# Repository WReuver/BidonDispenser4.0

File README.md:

# Bidon Dispenser 4.0
_Smart Solutions Semester - Join the Pipe - Year 17/18 - Semester 02_

### Authors
All the software is written by Robin C. Pel with student number 421 431. 
All the hardware is designed by Glen te Hofsté with student number 419 720. 

### Note to self
Use "git merge --allow-unrelated-histories [ORPHAN-BRANCH]" to merge orphan branches.

### While Loops
All the while loops in the Microcontroller's program:
- "./Communication/OneWire.cpp" line 13: Wait for a pin to be high
- "./Communication/USART.cpp" line 34: Wait for new data on the serial port
- "./Communication/USART.cpp" line 42: Wait for new data on the serial port for 2 seconds
- "./Hardware/SystemClock.cpp" line 13: Wait for the clock source to be ready
- "./Master/RaspberryPi.cpp" line 36: Wait until the pre-amble is found
- "./Sensors/DistanceSensor.cpp" line 93: Wait for a pin to be high
- "./Sensors/DistanceSensor.cpp" line 93: Wait for a pin to be low
- "./Sensors/TemperatureSensor.cpp" line 33: Wait for a pin to be high
- "./main.cpp" line 197, 280, 323, 362 and 384: Infinite loops

### Important
Not all code on the "microcontroller/software/develop" branch works with all the microcontroller hardware:  
	- All the commits **BEFORE** the tag "MCU_Festival" only work on the controller PCB v1.1  
	- All the commits **AFTER** the tag "MCU_Festival" only work on the controller PCB v2.0  
  
Another thing that's definitely worth mentioning is that on the microcontroller PCB v1.1 the ADC was used to read a 1 or 0.
This was done because for some weird reason it was not possible to read one of the digital pins, 
the microcontroller probably was broken or something but the decision was made to work around it for the time being.  
  
After the Smart Solutions Festival one of the distance sensors broke, this sensor was distance sensor number five.  
Distance Sensor Layout Layout (Top view, from the front):  
_Dist Sensor: [08] [01] [10] [03] [12] [05] [14] [07]_  
_Dist Sensor: [00] [09] [02] [11] [04] [13] [06] [15]_  

### Disclaimer
This was my first experience with C# and the Visual Studio IDE, there are probably a lot of things which could be optimized. 
This git repo was also misused a little bit, apologies. 
There is _no_ easter egg. 

### Regarding the UI Assets
All UI Assets were made using Paint dot net, you can get it here https://www.dotpdn.com/downloads/pdn.html

### The Team 💪

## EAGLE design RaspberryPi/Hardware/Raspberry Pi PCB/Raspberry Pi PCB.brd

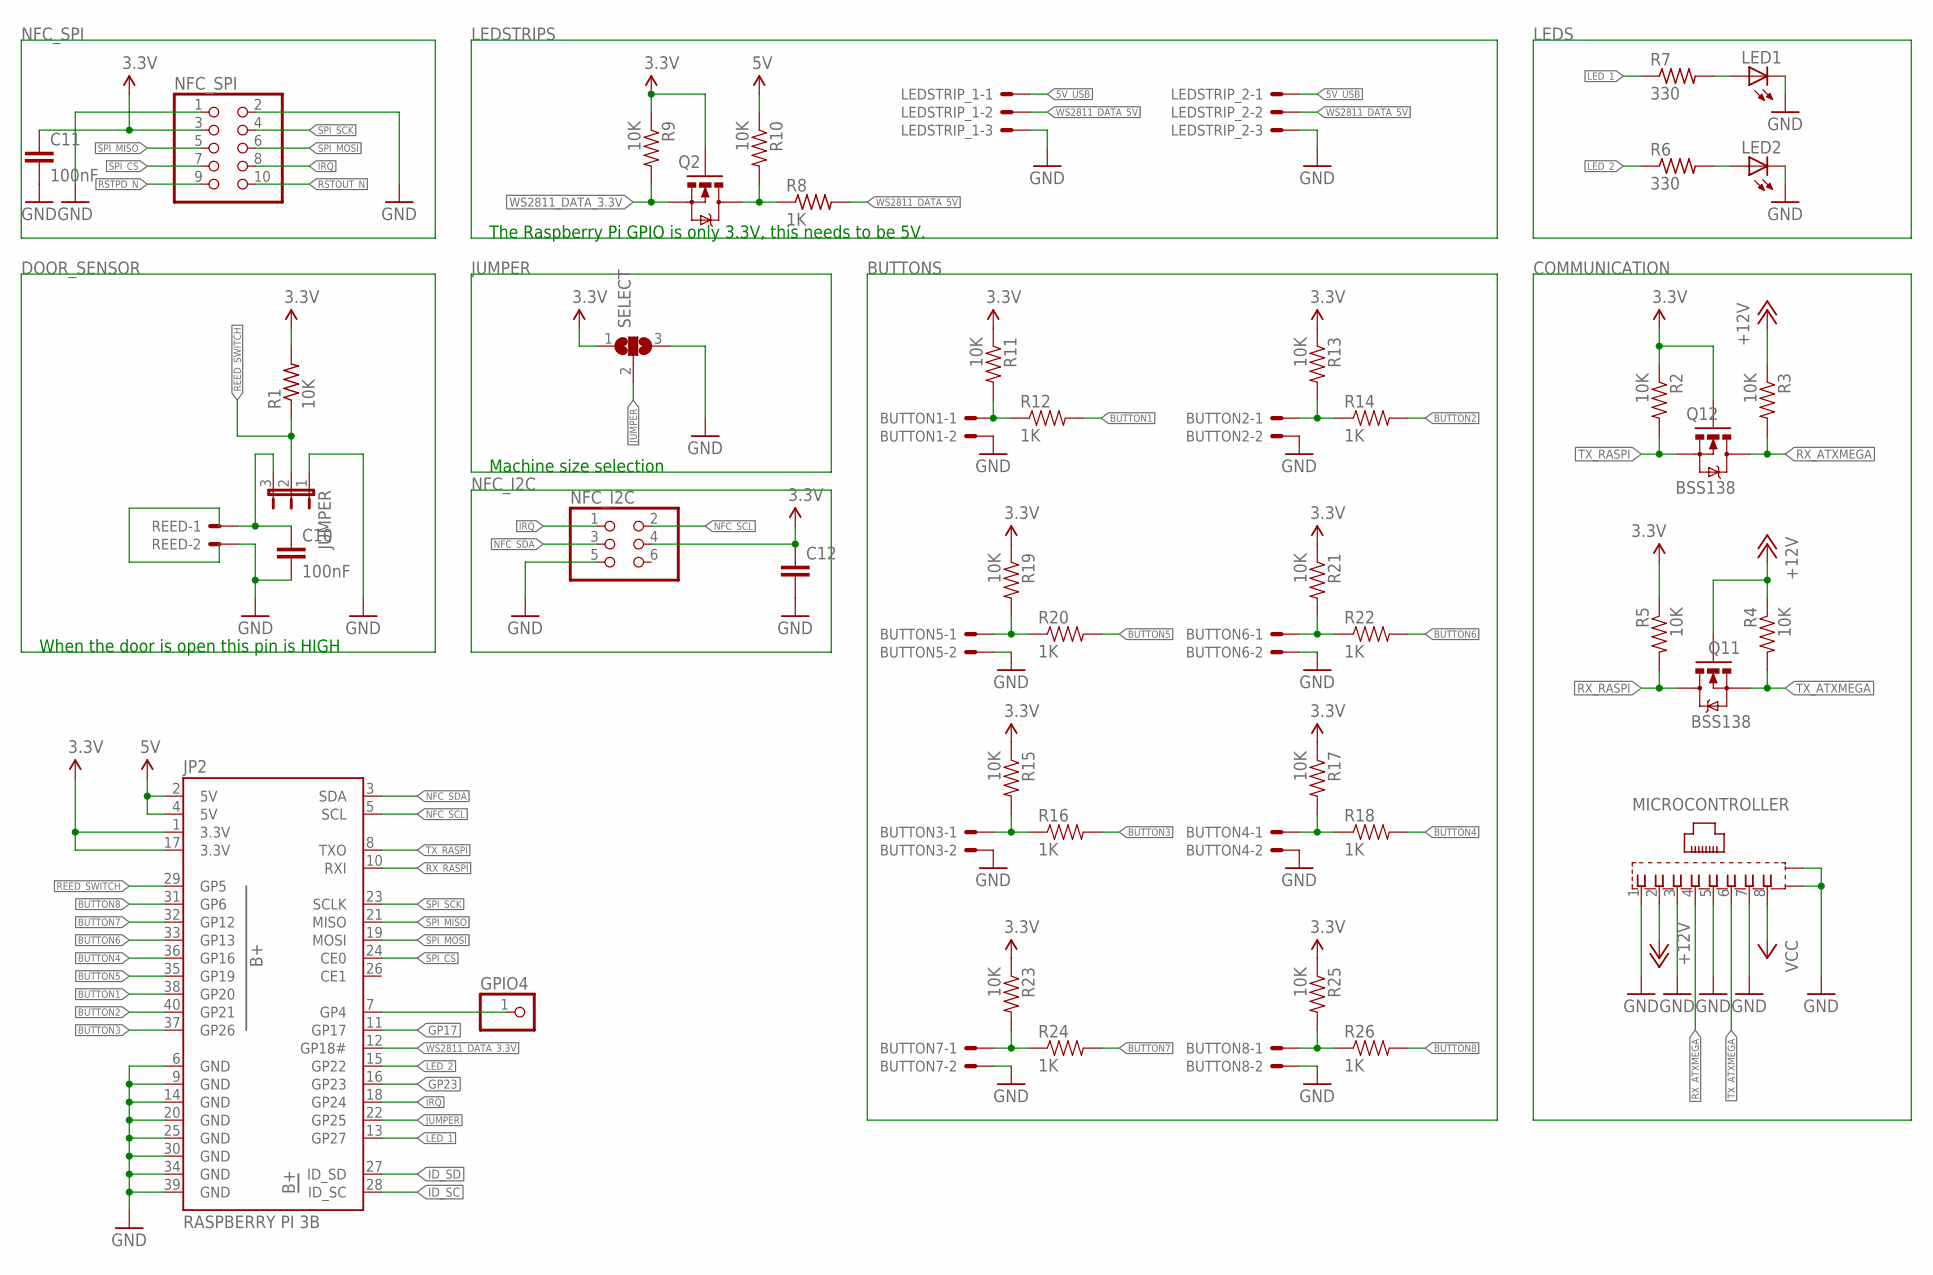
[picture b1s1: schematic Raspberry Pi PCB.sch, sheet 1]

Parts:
BUTTON1, BUTTON2, BUTTON3, BUTTON4, BUTTON5, BUTTON6, BUTTON7, BUTTON8: 22-05-7028-02; 7395-02
C10, C11, C12: 100nF; 0805
GPIO4: PINHD-1X1; 1X01
JP2: RASPBERRY PI 3B; 2X20-SHROUDED
JUMPER: JP2E; JP2
LED1, LED2: LEDCHIPLED_0805; CHIPLED_0805
LEDSTRIP_1, LEDSTRIP_2: 22-05-7038-03; 7395-03
MICROCONTROLLER: 0446200002
NFC_I2C: PINHD-2X3; 2X03
NFC_SPI: PINHD-2X5; 2X05
Q2, Q11, Q12: BSS138; SOT23-3
R1: 10K; R0805
R2, R3, R4, R5, R9, R10, R11, R13, R15, R17, R19, R21, R23, R25: 10K; 0603-RES
R6, R7: 330; R0805
R8: 1K; R0805
R12, R14, R16, R18, R20, R22, R24, R26: 1K; 0603-RES
REED: 22-05-7028-02; 7395-02
SELECT: SJ2W; SJ_2

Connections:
3.3V: C11.1, C12.1, JP2.1 (3.3V), JP2.17 (3.3V), NFC_I2C.4, NFC_SPI.3, Q2.1 (G), Q12.1 (G), R1.2, R2.1, R5.1, R9.1, R11.1, R13.1, R15.1, R17.1, R19.1, R21.1, R23.1, R25.1, SELECT.1
5V: JP2.2 (5V), JP2.4 (5V), R10.1; also elsewhere on the board
5V_USB: LEDSTRIP_1.1, LEDSTRIP_2.1; also elsewhere on the board
+12V: MICROCONTROLLER.2, Q11.1 (G), R3.1, R4.1
BUTTON1: JP2.38 (GP20), R12.2
BUTTON2: JP2.40 (GP21), R14.2
BUTTON3: JP2.37 (GP26), R16.2
BUTTON4: JP2.36 (GP16), R18.2
BUTTON5: JP2.35 (GP19), R20.2
BUTTON6: JP2.33 (GP13), R22.2
BUTTON7: JP2.32 (GP12), R24.2
BUTTON8: JP2.31 (GP6), R26.2
GND: BUTTON1.2, BUTTON2.2, BUTTON3.2, BUTTON4.2, BUTTON5.2, BUTTON6.2, BUTTON7.2, BUTTON8.2, C10.2, C11.2, C12.2, JP2.6 (GND), JP2.9 (GND), JP2.14 (GND), JP2.20 (GND), JP2.25 (GND), JP2.30 (GND), JP2.34 (GND), JP2.39 (GND), JUMPER.1, LED1.C, LED2.C, LEDSTRIP_1.3, LEDSTRIP_2.3, MICROCONTROLLER.1, MICROCONTROLLER.3, MICROCONTROLLER.5, MICROCONTROLLER.7, MICROCONTROLLER.S@1 (S1), MICROCONTROLLER.S@2 (S2), NFC_I2C.5, NFC_SPI.1, NFC_SPI.2, REED.2, SELECT.3; also elsewhere on the board
GP4: GPIO4.1, JP2.7 (GP4)
GP17: JP2.11 (GP17)
GP23: JP2.16 (GP23)
ID_SC: JP2.28 (ID_SC)
ID_SD: JP2.27 (ID_SD)
IRQ: JP2.18 (GP24), NFC_I2C.1, NFC_SPI.8
JUMPER: JP2.22 (GP25), SELECT.2
LED_1: JP2.13 (GP27), R7.1
LED_2: JP2.15 (GP22), R6.1
unnamed: C10.1, JUMPER.3, REED.1
unnamed: BUTTON2.1, R13.2, R14.1
unnamed: Q2.3 (D), R8.1, R10.2
unnamed: LED2.A, R6.2
unnamed: LED1.A, R7.2
unnamed: BUTTON1.1, R11.2, R12.1
unnamed: BUTTON3.1, R15.2, R16.1
unnamed: BUTTON4.1, R17.2, R18.1
unnamed: BUTTON5.1, R19.2, R20.1
unnamed: BUTTON6.1, R21.2, R22.1
unnamed: BUTTON7.1, R23.2, R24.1
unnamed: BUTTON8.1, R25.2, R26.1
NFC_SCL: JP2.5 (SCL), NFC_I2C.2
NFC_SDA: JP2.3 (SDA), NFC_I2C.3
REED_SWITCH: JP2.29 (GP5), JUMPER.2, R1.1
RSTOUT_N: NFC_SPI.10
RSTPD_N: NFC_SPI.9
RX_ATXMEGA: MICROCONTROLLER.4, Q12.3 (D), R3.2
RX_RASPI: JP2.10 (RXI), Q11.3 (D), R5.2
SPI_CS: JP2.24 (CE0), NFC_SPI.7
SPI_MISO: JP2.21 (MISO), NFC_SPI.5
SPI_MOSI: JP2.19 (MOSI), NFC_SPI.6
SPI_SCK: JP2.23 (SCLK), NFC_SPI.4
TX_ATXMEGA: MICROCONTROLLER.6, Q11.2 (S), R4.2
TX_RASPI: JP2.8 (TXO), Q12.2 (S), R2.2
VCC: MICROCONTROLLER.8
WS2811_DATA_3.3V: JP2.12 (GP18#), Q2.2 (S), R9.2
WS2811_DATA_5V: LEDSTRIP_1.2, LEDSTRIP_2.2, R8.2

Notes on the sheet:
Machine size selection
When the door is open this pin is HIGH
The Raspberry Pi GPIO is only 3.3V, this needs to be 5V.

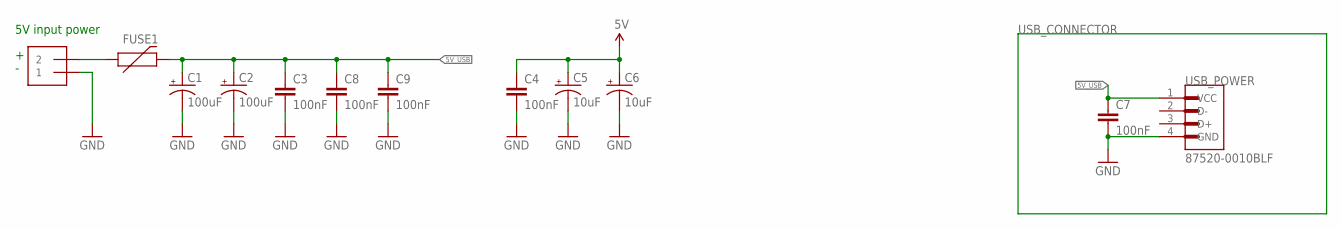
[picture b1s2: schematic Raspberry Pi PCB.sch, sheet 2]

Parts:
C1, C2: 100uF; 175TMP-0810
C3, C4, C7, C8, C9: 100nF; 0805
C5, C6: 10uF; 153CLV-0505
FUSE1: 6V/0.5A; 1206
INPUT: 1X2-3.5MM
USB_POWER: 87520-0010BLF; FCI_87520-0010BLF

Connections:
5V: C4.1, C5.+, C6.+; also elsewhere on the board
5V_USB: C1.+, C2.+, C3.1, C7.1, C8.1, C9.1, FUSE1.2, USB_POWER.1 (VCC); also elsewhere on the board
GND: C1.-, C2.-, C3.2, C4.2, C5.-, C6.-, C7.2, C8.2, C9.2, INPUT.1, USB_POWER.4 (GND); also elsewhere on the board
VIN1: FUSE1.1, INPUT.2

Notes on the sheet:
5V input power

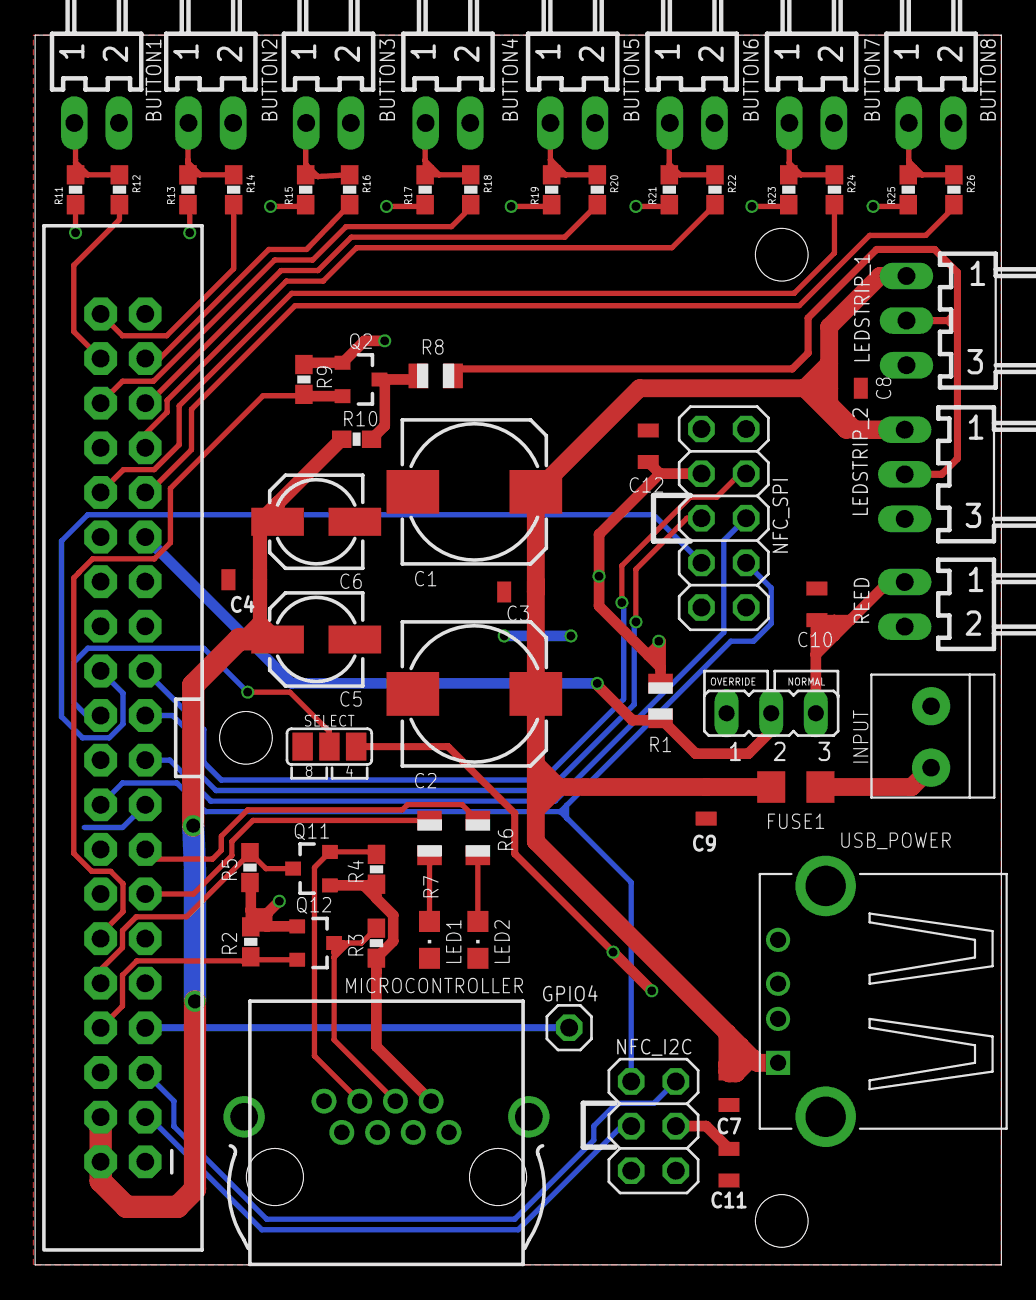
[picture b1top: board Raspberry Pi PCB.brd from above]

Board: 2 copper layers, 55.0 x 70.0 mm, 64 parts (0 on the bottom side), 44 nets.

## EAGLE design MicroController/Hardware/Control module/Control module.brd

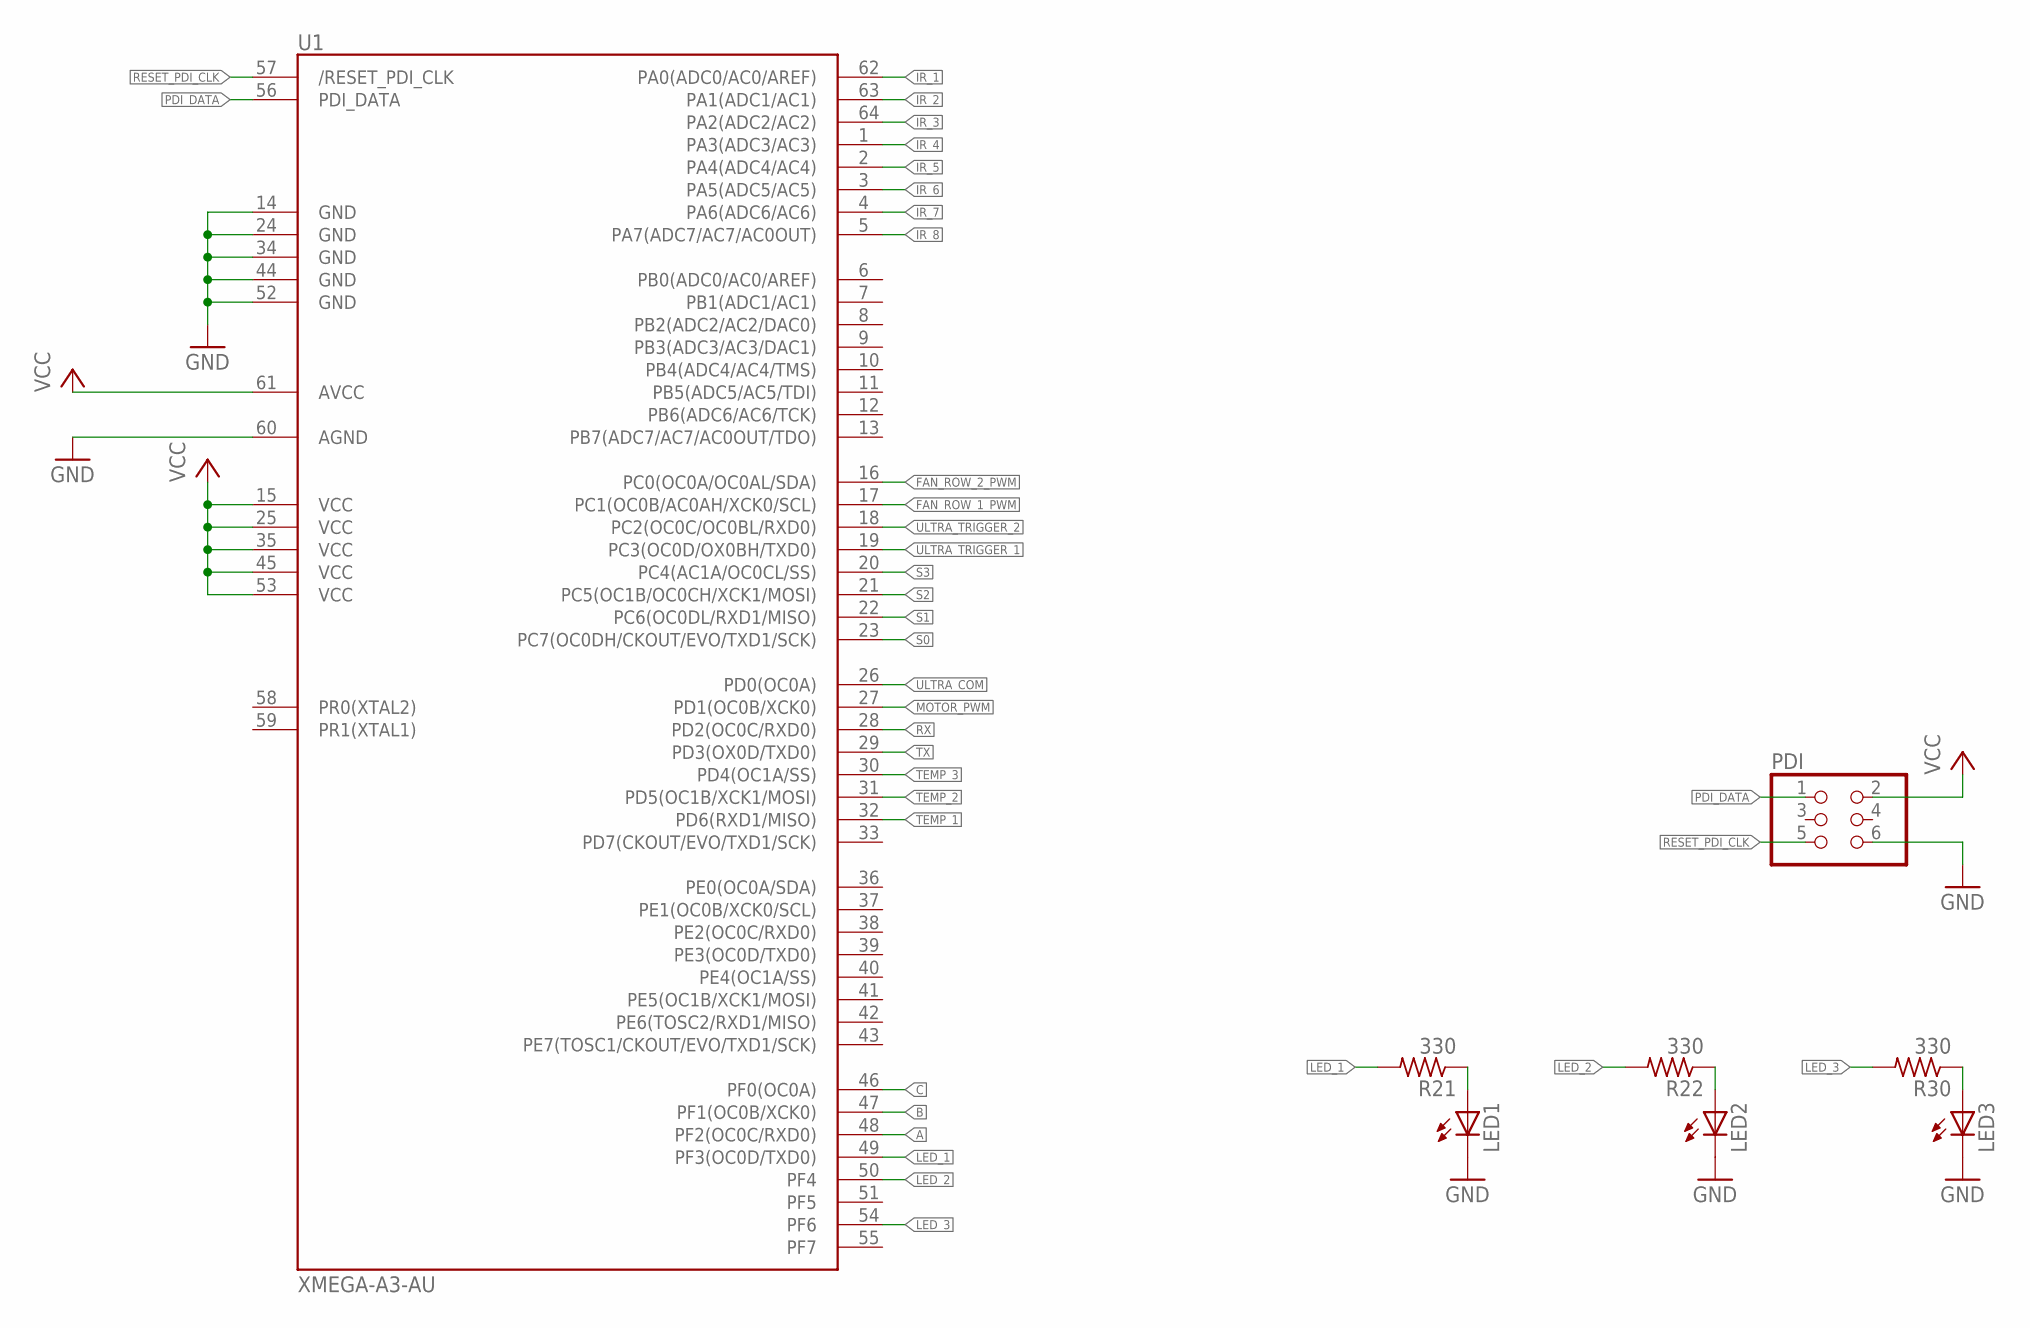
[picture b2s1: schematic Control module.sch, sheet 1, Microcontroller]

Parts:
LED1, LED2, LED3: LEDCHIPLED_0805; CHIPLED_0805
PDI: PINHD-2X3; 2X03
R21, R22, R30: 330; R0805
U1: XMEGA-A3-AU; TQFP64_14X14MM_MCU

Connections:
A: U1.48 (PF2(OC0C/RXD0)); also elsewhere on the board
B: U1.47 (PF1(OC0B/XCK0)); also elsewhere on the board
C: U1.46 (PF0(OC0A)); also elsewhere on the board
FAN_ROW_1_PWM: U1.17 (PC1(OC0B/AC0AH/XCK0/SCL)); also elsewhere on the board
FAN_ROW_2_PWM: U1.16 (PC0(OC0A/OC0AL/SDA)); also elsewhere on the board
GND: LED1.C, LED2.C, LED3.C, PDI.6, U1.14 (GND1), U1.24 (GND2), U1.34 (GND3), U1.44 (GND4), U1.52 (GND5), U1.60 (AGND); also elsewhere on the board
IR_1: U1.62 (PA0(ADC0/AC0/AREF)); also elsewhere on the board
IR_2: U1.63 (PA1(ADC1/AC1)); also elsewhere on the board
IR_3: U1.64 (PA2(ADC2/AC2)); also elsewhere on the board
IR_4: U1.1 (PA3(ADC3/AC3)); also elsewhere on the board
IR_5: U1.2 (PA4(ADC4/AC4)); also elsewhere on the board
IR_6: U1.3 (PA5(ADC5/AC5)); also elsewhere on the board
IR_7: U1.4 (PA6(ADC6/AC6)); also elsewhere on the board
IR_8: U1.5 (PA7(ADC7/AC7/AC0OUT)); also elsewhere on the board
LED_1: R21.2, U1.49 (PF3(OC0D/TXD0))
LED_2: R22.2, U1.50 (PF4)
LED_3: R30.2, U1.54 (PF6)
MOTOR_PWM: U1.27 (PD1(OC0B/XCK0)); also elsewhere on the board
unnamed: LED2.A, R22.1
unnamed: LED1.A, R21.1
unnamed: LED3.A, R30.1
PDI_DATA: PDI.1, U1.56 (PDI_DATA)
RESET_PDI_CLK: PDI.5, U1.57 (/RESET_PDI_CLK)
RX: U1.28 (PD2(OC0C/RXD0)); also elsewhere on the board
S0: U1.23 (PC7(OC0DH/CKOUT/EVO/TXD1/SCK)); also elsewhere on the board
S1: U1.22 (PC6(OC0DL/RXD1/MISO)); also elsewhere on the board
S2: U1.21 (PC5(OC1B/OC0CH/XCK1/MOSI)); also elsewhere on the board
S3: U1.20 (PC4(AC1A/OC0CL/SS)); also elsewhere on the board
TEMP_1: U1.32 (PD6(RXD1/MISO)); also elsewhere on the board
TEMP_2: U1.31 (PD5(OC1B/XCK1/MOSI)); also elsewhere on the board
TEMP_3: U1.30 (PD4(OC1A/SS)); also elsewhere on the board
TX: U1.29 (PD3(OX0D/TXD0)); also elsewhere on the board
ULTRA_COM: U1.26 (PD0(OC0A)); also elsewhere on the board
ULTRA_TRIGGER_1: U1.19 (PC3(OC0D/OX0BH/TXD0)); also elsewhere on the board
ULTRA_TRIGGER_2: U1.18 (PC2(OC0C/OC0BL/RXD0)); also elsewhere on the board
VCC: PDI.2, U1.15 (VCC1), U1.25 (VCC2), U1.35 (VCC3), U1.45 (VCC4), U1.53 (VCC5), U1.61 (AVCC); also elsewhere on the board

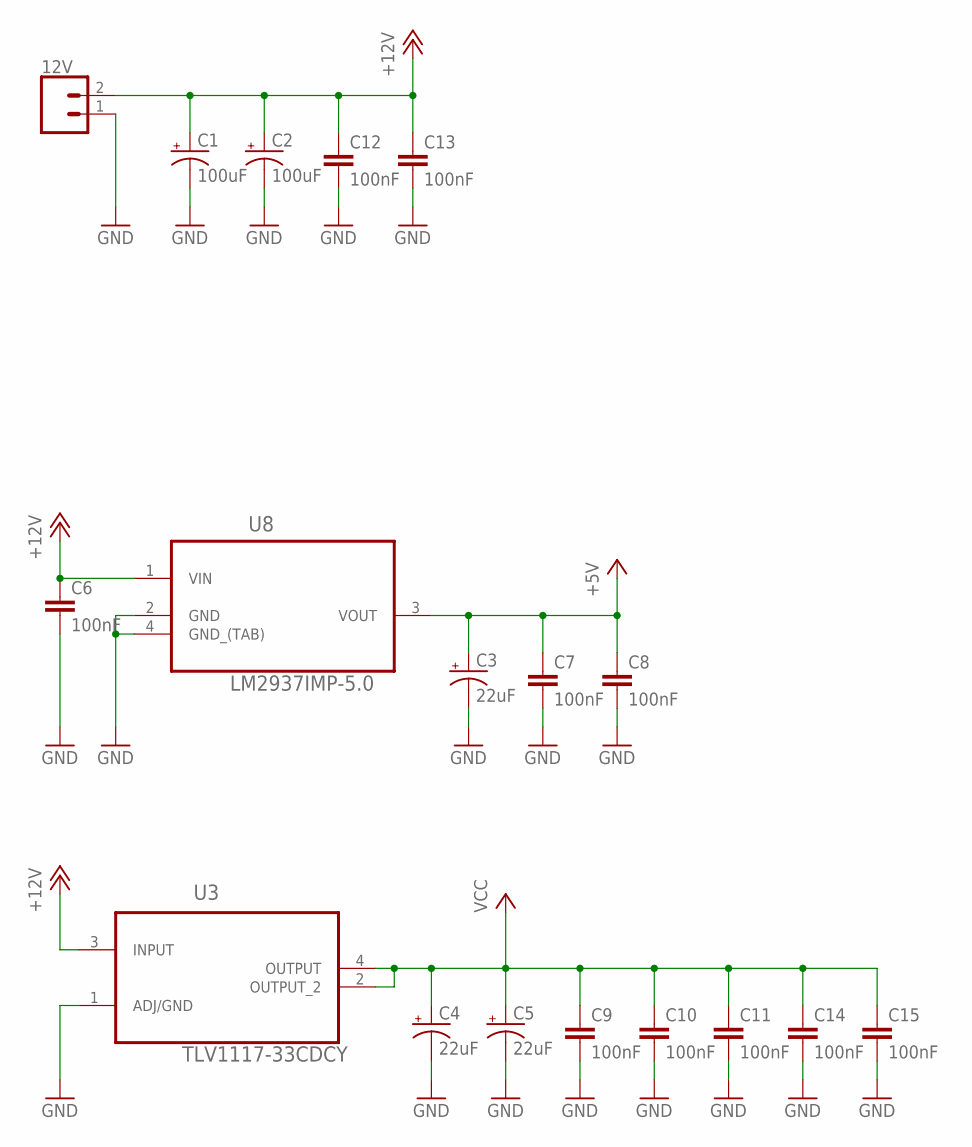
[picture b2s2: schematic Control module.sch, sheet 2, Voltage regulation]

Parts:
12V: CONN_025MM; SCREWTERMINAL-5MM-2
C1, C2: 100uF; 150CLZ-0810
C3, C4, C5: 22uF; 153CLV-0505
C6, C7, C8, C9, C10, C11, C12, C13, C14, C15: 100nF; 0805
U3: TLV1117-33CDCY; SOT230P700X180-4N
U8: LM2937IMP-5.0; SOT230P700X180-4N

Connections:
+5V: C3.+, C7.1, C8.1, U8.3 (VOUT); also elsewhere on the board
+12V: 12V.2, C1.+, C2.+, C6.1, C12.1, C13.1, U3.3 (INPUT), U8.1 (VIN); also elsewhere on the board
GND: 12V.1, C1.-, C2.-, C3.-, C4.-, C5.-, C6.2, C7.2, C8.2, C9.2, C10.2, C11.2, C12.2, C13.2, C14.2, C15.2, U3.1 (ADJ/GND), U8.2 (GND), U8.4 (GND_(TAB)); also elsewhere on the board
VCC: C4.+, C5.+, C9.1, C10.1, C11.1, C14.1, C15.1, U3.2 (OUTPUT_2), U3.4 (OUTPUT); also elsewhere on the board

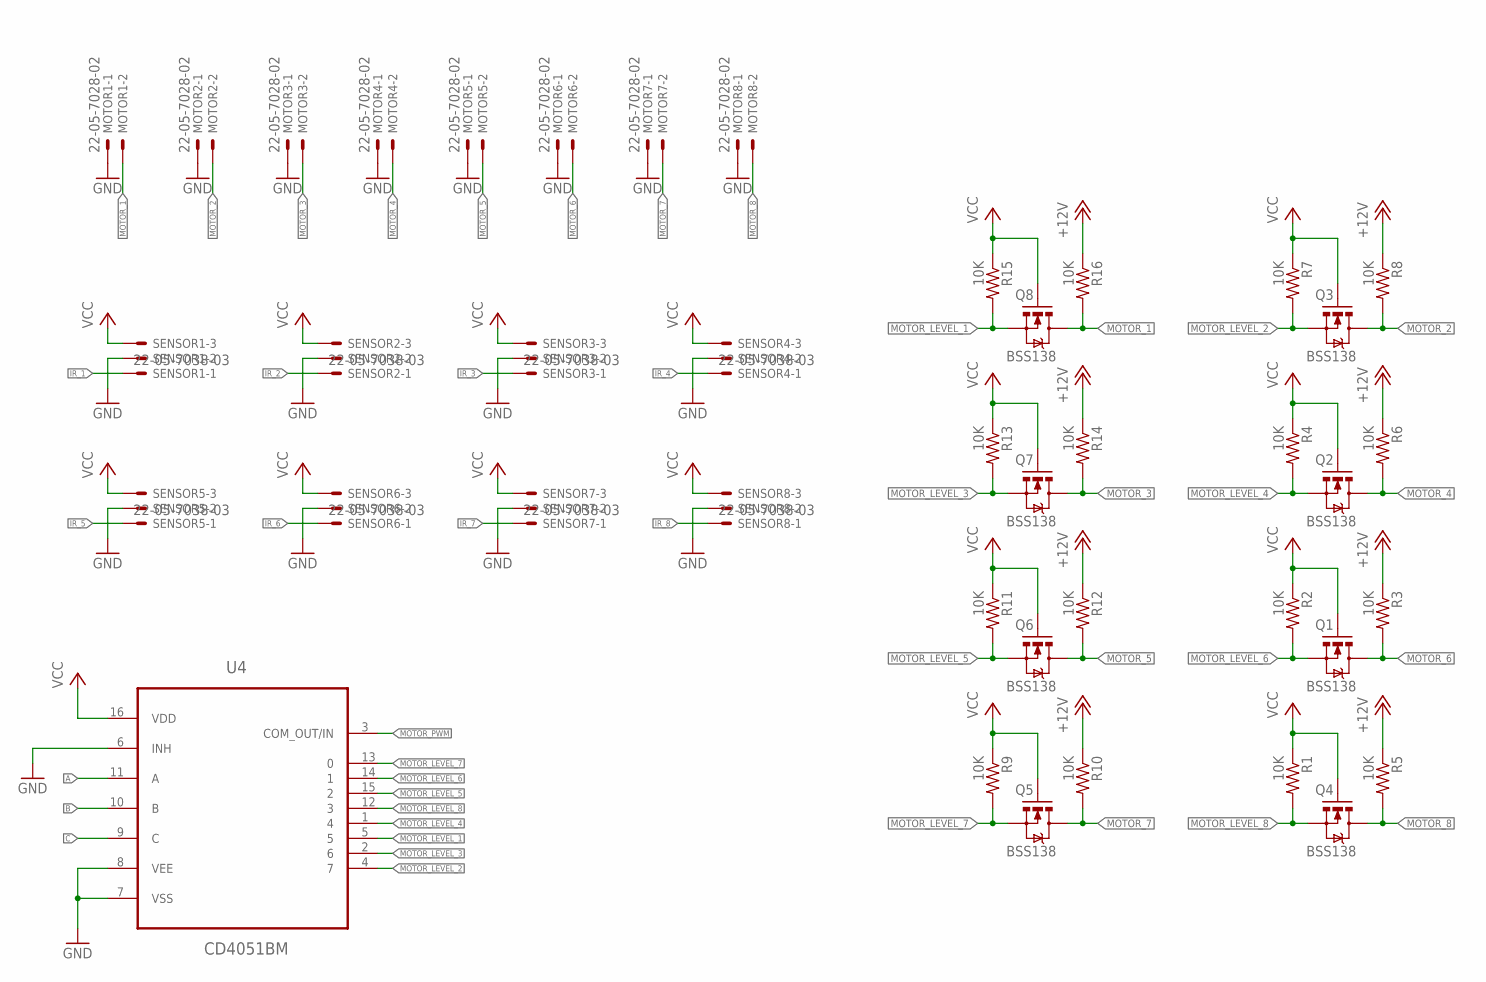
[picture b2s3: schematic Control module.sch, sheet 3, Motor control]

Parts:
MOTOR1, MOTOR2, MOTOR3, MOTOR4, MOTOR5, MOTOR6, MOTOR7, MOTOR8: 22-05-7028-02; 7395-02
Q1, Q2, Q3, Q4, Q5, Q6, Q7, Q8: BSS138; SOT23-3
R1, R2, R3, R4, R5, R6, R7, R8, R9, R10, R11, R12, R13, R14, R15, R16: 10K; 0603-RES
SENSOR1, SENSOR2, SENSOR3, SENSOR4, SENSOR5, SENSOR6, SENSOR7, SENSOR8: 22-05-7038-03; 7395-03
U4: CD4051BM; SOIC127P600X175-16N

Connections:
+12V: R3.1, R5.1, R6.1, R8.1, R10.1, R12.1, R14.1, R16.1; also elsewhere on the board
A: U4.11 (A); also elsewhere on the board
B: U4.10 (B); also elsewhere on the board
C: U4.9 (C); also elsewhere on the board
GND: MOTOR1.1, MOTOR2.1, MOTOR3.1, MOTOR4.1, MOTOR5.1, MOTOR6.1, MOTOR7.1, MOTOR8.1, SENSOR1.2, SENSOR2.2, SENSOR3.2, SENSOR4.2, SENSOR5.2, SENSOR6.2, SENSOR7.2, SENSOR8.2, U4.6 (INH), U4.7 (VSS), U4.8 (VEE); also elsewhere on the board
IR_1: SENSOR1.1; also elsewhere on the board
IR_2: SENSOR2.1; also elsewhere on the board
IR_3: SENSOR3.1; also elsewhere on the board
IR_4: SENSOR4.1; also elsewhere on the board
IR_5: SENSOR5.1; also elsewhere on the board
IR_6: SENSOR6.1; also elsewhere on the board
IR_7: SENSOR7.1; also elsewhere on the board
IR_8: SENSOR8.1; also elsewhere on the board
MOTOR_1: MOTOR1.2, Q8.3 (D), R16.2
MOTOR_2: MOTOR2.2, Q3.3 (D), R8.2
MOTOR_3: MOTOR3.2, Q7.3 (D), R14.2
MOTOR_4: MOTOR4.2, Q2.3 (D), R6.2
MOTOR_5: MOTOR5.2, Q6.3 (D), R12.2
MOTOR_6: MOTOR6.2, Q1.3 (D), R3.2
MOTOR_7: MOTOR7.2, Q5.3 (D), R10.2
MOTOR_8: MOTOR8.2, Q4.3 (D), R5.2
MOTOR_LEVEL_1: Q8.2 (S), R15.2, U4.5
MOTOR_LEVEL_2: Q3.2 (S), R7.2, U4.4 (7)
MOTOR_LEVEL_3: Q7.2 (S), R13.2, U4.2 (6)
MOTOR_LEVEL_4: Q2.2 (S), R4.2, U4.1 (4)
MOTOR_LEVEL_5: Q6.2 (S), R11.2, U4.15 (2)
MOTOR_LEVEL_6: Q1.2 (S), R2.2, U4.14 (1)
MOTOR_LEVEL_7: Q5.2 (S), R9.2, U4.13 (0)
MOTOR_LEVEL_8: Q4.2 (S), R1.2, U4.12 (3)
MOTOR_PWM: U4.3 (COM_OUT/IN); also elsewhere on the board
VCC: Q1.1 (G), Q2.1 (G), Q3.1 (G), Q4.1 (G), Q5.1 (G), Q6.1 (G), Q7.1 (G), Q8.1 (G), R1.1, R2.1, R4.1, R7.1, R9.1, R11.1, R13.1, R15.1, SENSOR1.3, SENSOR2.3, SENSOR3.3, SENSOR4.3, SENSOR5.3, SENSOR6.3, SENSOR7.3, SENSOR8.3, U4.16 (VDD); also elsewhere on the board

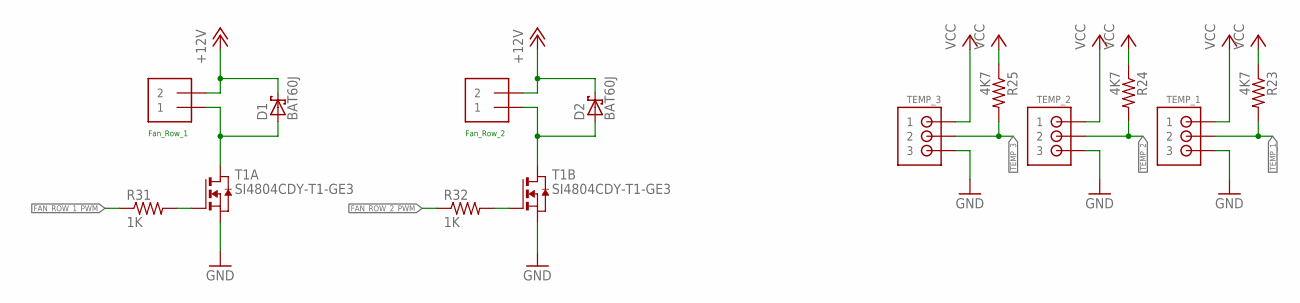
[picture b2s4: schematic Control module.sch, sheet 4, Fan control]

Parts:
D1, D2: BAT60J; SOD323_ST
FAN_1, FAN_2: 1X2-3.5MM
R23, R24, R25: 4K7; R0805
R31, R32: 1K; 0603-RES
T1: SI4804CDY-T1-GE3; SO8
TEMP_1, TEMP_2, TEMP_3: JST-PH_3-PIN_HEADER; JST_B3B-PH_HEADER

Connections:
+12V: D1.C, D2.C, FAN_1.2, FAN_2.2; also elsewhere on the board
FAN_ROW_1_PWM: R31.1; also elsewhere on the board
FAN_ROW_2_PWM: R32.1; also elsewhere on the board
GND: T1.1 (S), T1.3 (S), TEMP_1.P3 (3), TEMP_2.P3 (3), TEMP_3.P3 (3); also elsewhere on the board
unnamed: R31.2, T1.2 (G)
unnamed: D2.A, FAN_2.1, T1.5 (D), T1.6 (D)
unnamed: R32.2, T1.4 (G)
unnamed: D1.A, FAN_1.1, T1.7 (D), T1.8 (D)
TEMP_1: R23.2, TEMP_1.P2 (2); also elsewhere on the board
TEMP_2: R24.2, TEMP_2.P2 (2); also elsewhere on the board
TEMP_3: R25.2, TEMP_3.P2 (2); also elsewhere on the board
VCC: R23.1, R24.1, R25.1, TEMP_1.P1 (1), TEMP_2.P1 (1), TEMP_3.P1 (1); also elsewhere on the board

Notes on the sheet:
Fan_Row_2
Fan_Row_1

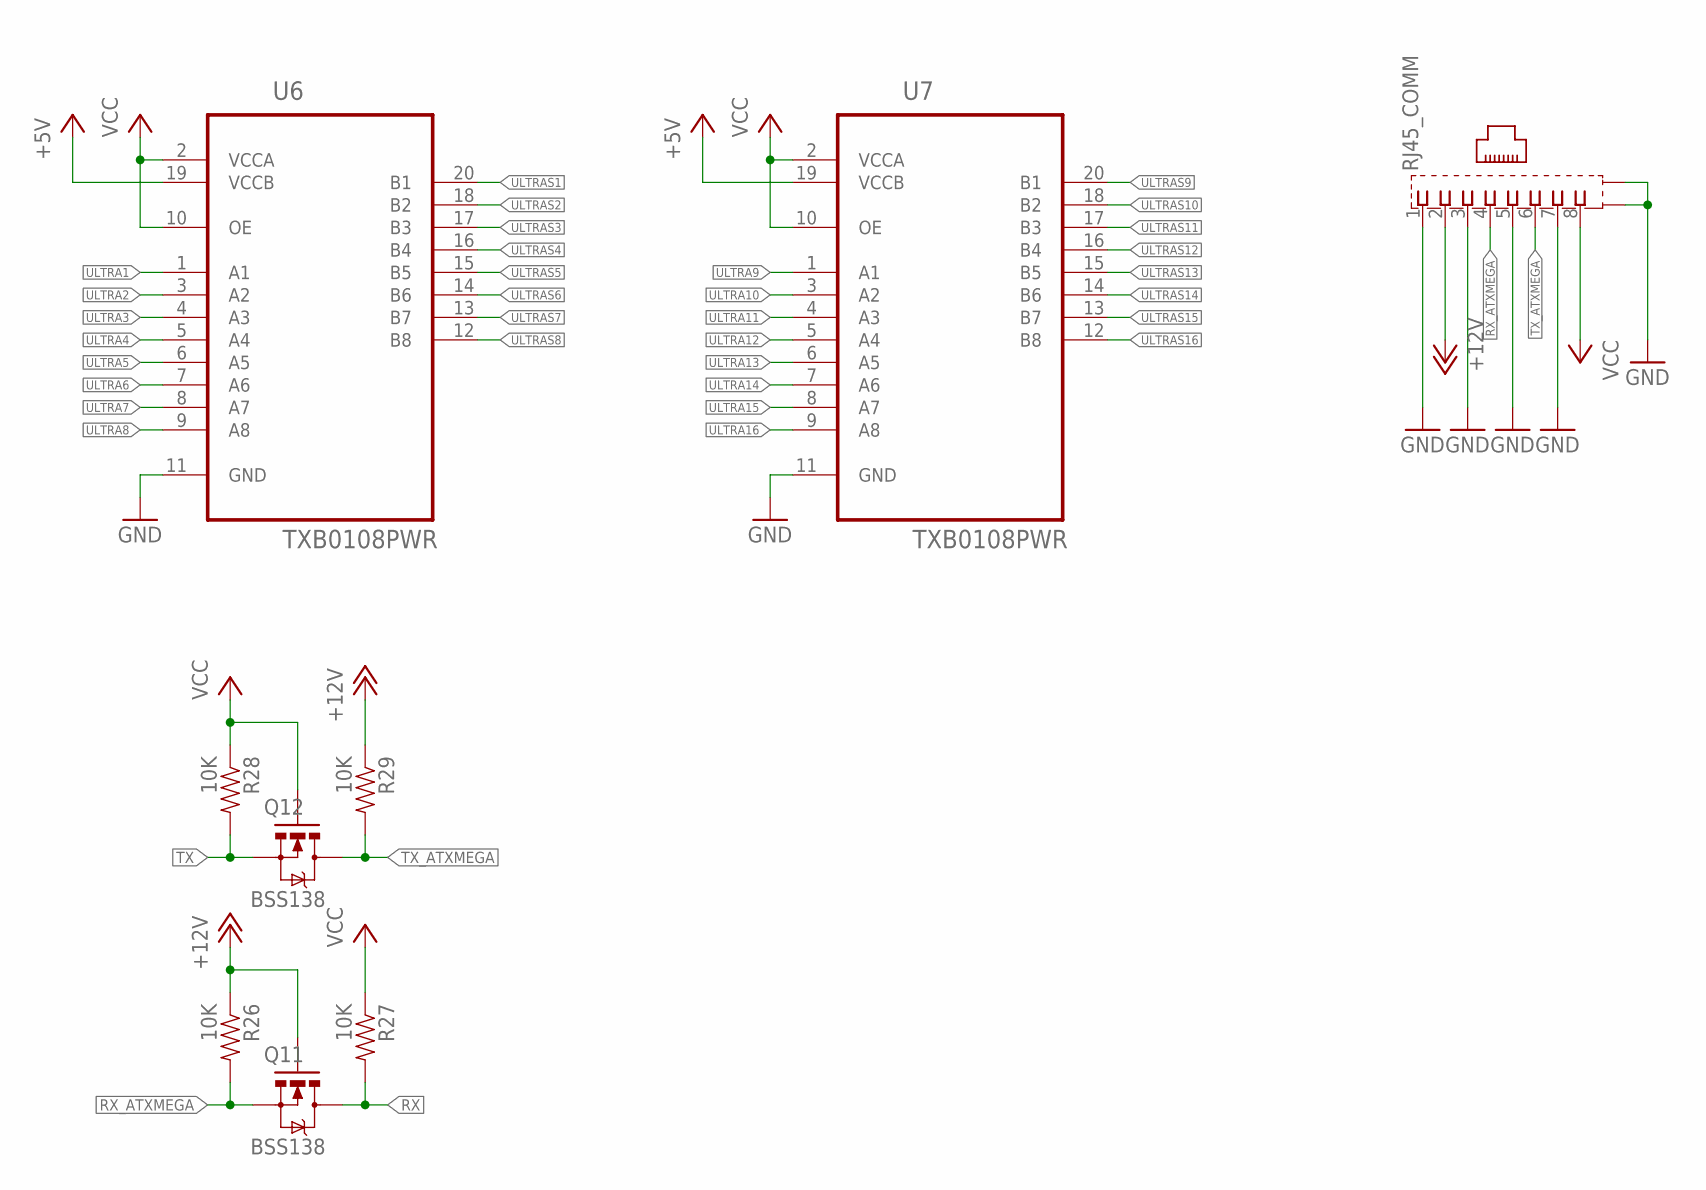
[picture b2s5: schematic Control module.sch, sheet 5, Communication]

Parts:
Q11, Q12: BSS138; SOT23-3
R26, R27, R28, R29: 10K; 0603-RES
RJ45_COMM: 0446200002
U6, U7: TXB0108PWR; SOP65P640X120-20N

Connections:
+5V: U6.19 (VCCB), U7.19 (VCCB); also elsewhere on the board
+12V: Q11.1 (G), R26.1, R29.1, RJ45_COMM.2; also elsewhere on the board
GND: RJ45_COMM.1, RJ45_COMM.3, RJ45_COMM.5, RJ45_COMM.7, RJ45_COMM.S@1 (S1), RJ45_COMM.S@2 (S2), U6.11 (GND), U7.11 (GND); also elsewhere on the board
RX: Q11.3 (D), R27.2; also elsewhere on the board
RX_ATXMEGA: Q11.2 (S), R26.2, RJ45_COMM.4
TX: Q12.2 (S), R28.2; also elsewhere on the board
TX_ATXMEGA: Q12.3 (D), R29.2, RJ45_COMM.6
ULTRA1: U6.1 (A1); also elsewhere on the board
ULTRA2: U6.3 (A2); also elsewhere on the board
ULTRA3: U6.4 (A3); also elsewhere on the board
ULTRA4: U6.5 (A4); also elsewhere on the board
ULTRA5: U6.6 (A5); also elsewhere on the board
ULTRA6: U6.7 (A6); also elsewhere on the board
ULTRA7: U6.8 (A7); also elsewhere on the board
ULTRA8: U6.9 (A8); also elsewhere on the board
ULTRA9: U7.1 (A1); also elsewhere on the board
ULTRA10: U7.3 (A2); also elsewhere on the board
ULTRA11: U7.4 (A3); also elsewhere on the board
ULTRA12: U7.5 (A4); also elsewhere on the board
ULTRA13: U7.6 (A5); also elsewhere on the board
ULTRA14: U7.7 (A6); also elsewhere on the board
ULTRA15: U7.8 (A7); also elsewhere on the board
ULTRA16: U7.9 (A8); also elsewhere on the board
ULTRAS1: U6.20 (B1); also elsewhere on the board
ULTRAS2: U6.18 (B2); also elsewhere on the board
ULTRAS3: U6.17 (B3); also elsewhere on the board
ULTRAS4: U6.16 (B4); also elsewhere on the board
ULTRAS5: U6.15 (B5); also elsewhere on the board
ULTRAS6: U6.14 (B6); also elsewhere on the board
ULTRAS7: U6.13 (B7); also elsewhere on the board
ULTRAS8: U6.12 (B8); also elsewhere on the board
ULTRAS9: U7.20 (B1); also elsewhere on the board
ULTRAS10: U7.18 (B2); also elsewhere on the board
ULTRAS11: U7.17 (B3); also elsewhere on the board
ULTRAS12: U7.16 (B4); also elsewhere on the board
ULTRAS13: U7.15 (B5); also elsewhere on the board
ULTRAS14: U7.14 (B6); also elsewhere on the board
ULTRAS15: U7.13 (B7); also elsewhere on the board
ULTRAS16: U7.12 (B8); also elsewhere on the board
VCC: Q12.1 (G), R27.1, R28.1, RJ45_COMM.8, U6.2 (VCCA), U6.10 (OE), U7.2 (VCCA), U7.10 (OE); also elsewhere on the board

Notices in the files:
parts and their libraries:
SparkFun-Retired: Licensing: Creative Commons ShareAlike 4.0 International - https://creativecommons.org/licenses/by-sa/4.0
SparkFun-Boards: Licensing: CC v3.0 Share-Alike You are welcome to use this library for commercial purposes.
